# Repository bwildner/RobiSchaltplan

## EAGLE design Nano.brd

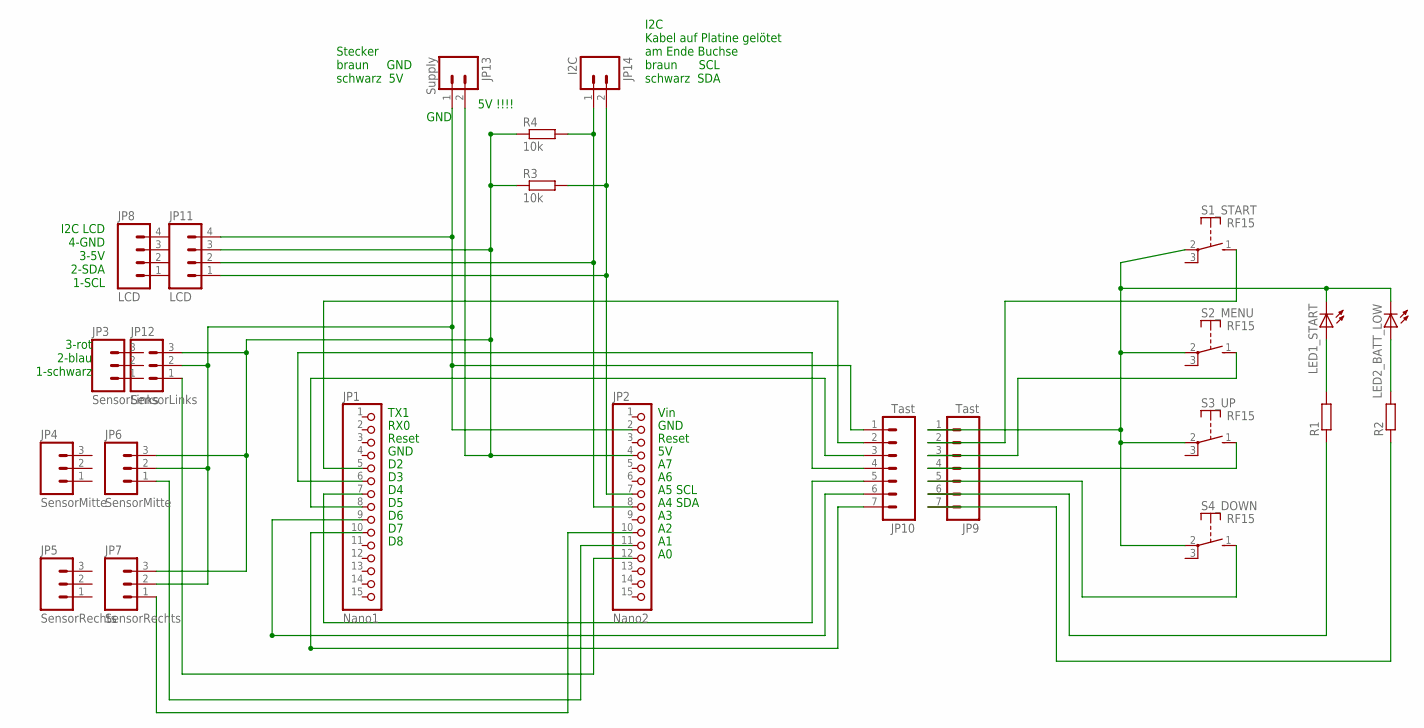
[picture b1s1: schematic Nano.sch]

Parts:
JP1: Nano1; 1X15
JP2: Nano2; 1X15
JP3, JP12: SensorLinks; 1X03_LOCK
JP4, JP6: SensorMitte; 1X03_LOCK
JP5, JP7: SensorRechts; 1X03_LOCK
JP8, JP11: LCD; 1X04_LOCK
JP9, JP10: Tast; 1X07
JP13: Supply; 1X02_LOCK
JP14: I2C; 1X02_LOCK
LED1_START, LED2_BATT_LOW: LED_ELD260; LED_LD260
R1, R2: R-EU_0204/5; 0204/5
R3, R4: 10k; 0204/5
S1_START, S2_MENU, S3_UP, S4_DOWN: RF15

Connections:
GND: JP9.1, LED1_START.K (C), LED2_BATT_LOW.K (C), S1_START.2, S2_MENU.2, S3_UP.2, S4_DOWN.2
unnamed: JP1.5, JP10.2
unnamed: JP1.8, JP10.3
unnamed: JP1.6, JP10.4
unnamed: JP1.7, JP10.5
unnamed: JP9.7, R2.1
unnamed: LED2_BATT_LOW.A, R2.2
unnamed: LED1_START.A, R1.2
unnamed: JP1.9, JP10.6
unnamed: JP2.12, JP12.1
unnamed: JP2.11, JP6.1
unnamed: JP2.10, JP7.1
unnamed: JP2.4, JP6.3, JP7.3, JP11.3, JP12.3, JP13.2, R3.1, R4.1
unnamed: JP2.2, JP6.2, JP7.2, JP10.1, JP11.4, JP12.2, JP13.1
unnamed: JP2.7, JP11.1, JP14.2, R3.2
unnamed: JP2.8, JP11.2, JP14.1, R4.2
unnamed: JP9.2, S1_START.1 (S)
unnamed: JP9.4, S3_UP.1 (S)
unnamed: JP9.3, S2_MENU.1 (S)
unnamed: JP9.5, S4_DOWN.1 (S)
unnamed: JP9.6, R1.1
unnamed: JP1.10, JP10.7

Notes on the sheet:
TX1
RX0
Reset
GND
Vin
A5 SCL
A4 SDA
Stecker braun GND schwarz 5V
5V !!!!
I2C Kabel auf Platine gelötet am Ende Buchse braun SCL schwarz SDA
I2C LCD 4-GND 3-5V 2-SDA 1-SCL
3-rot 2-blau 1-schwarz

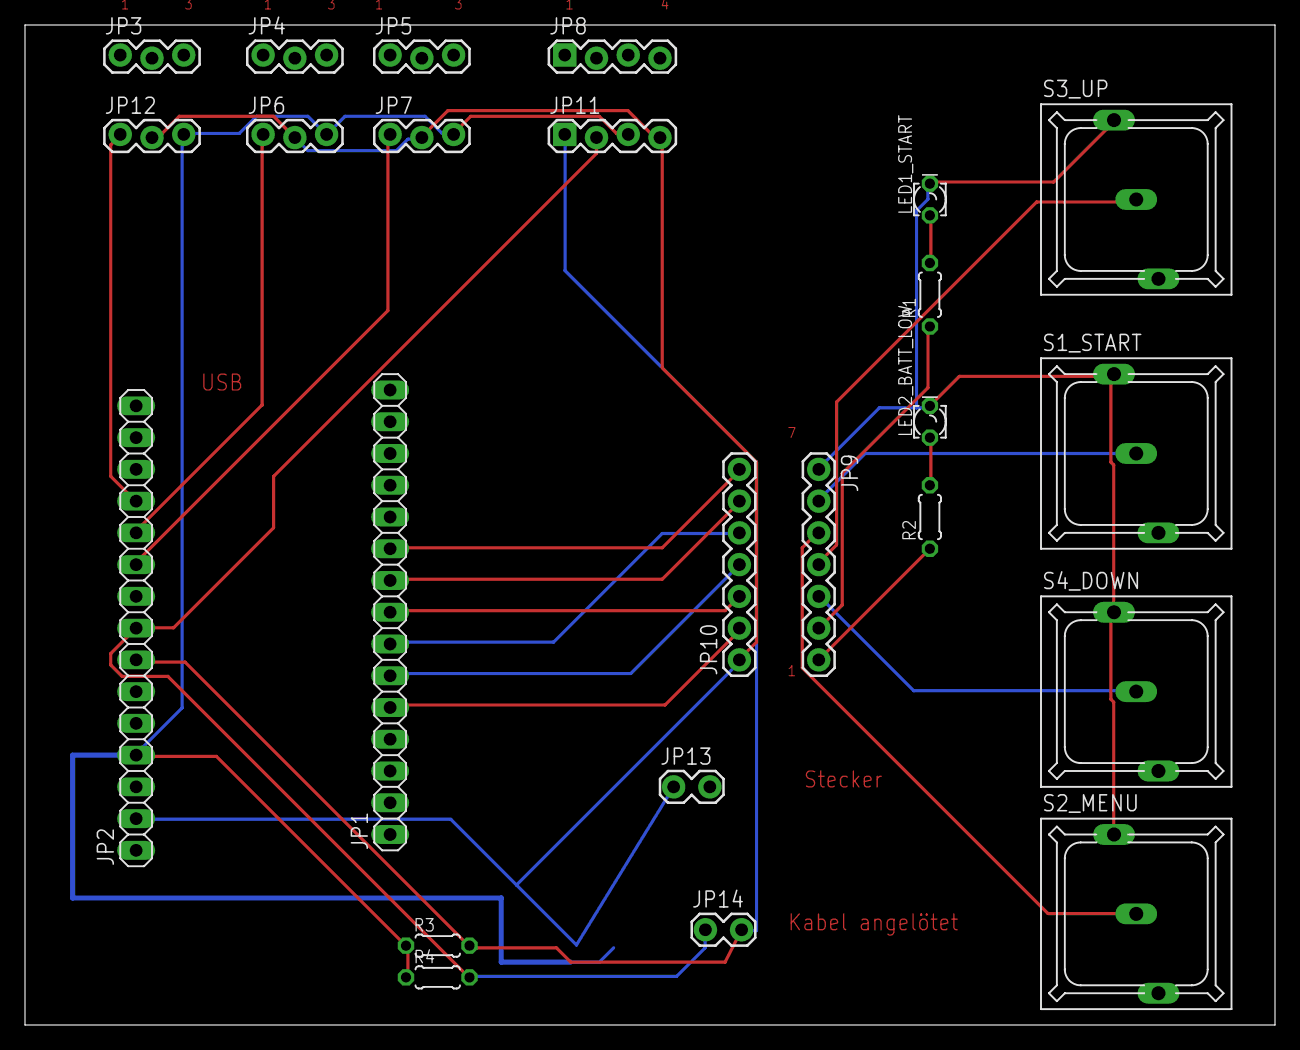
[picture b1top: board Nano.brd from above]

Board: 2 copper layers, 100.0 x 80.0 mm, 24 parts (0 on the bottom side), 22 nets.

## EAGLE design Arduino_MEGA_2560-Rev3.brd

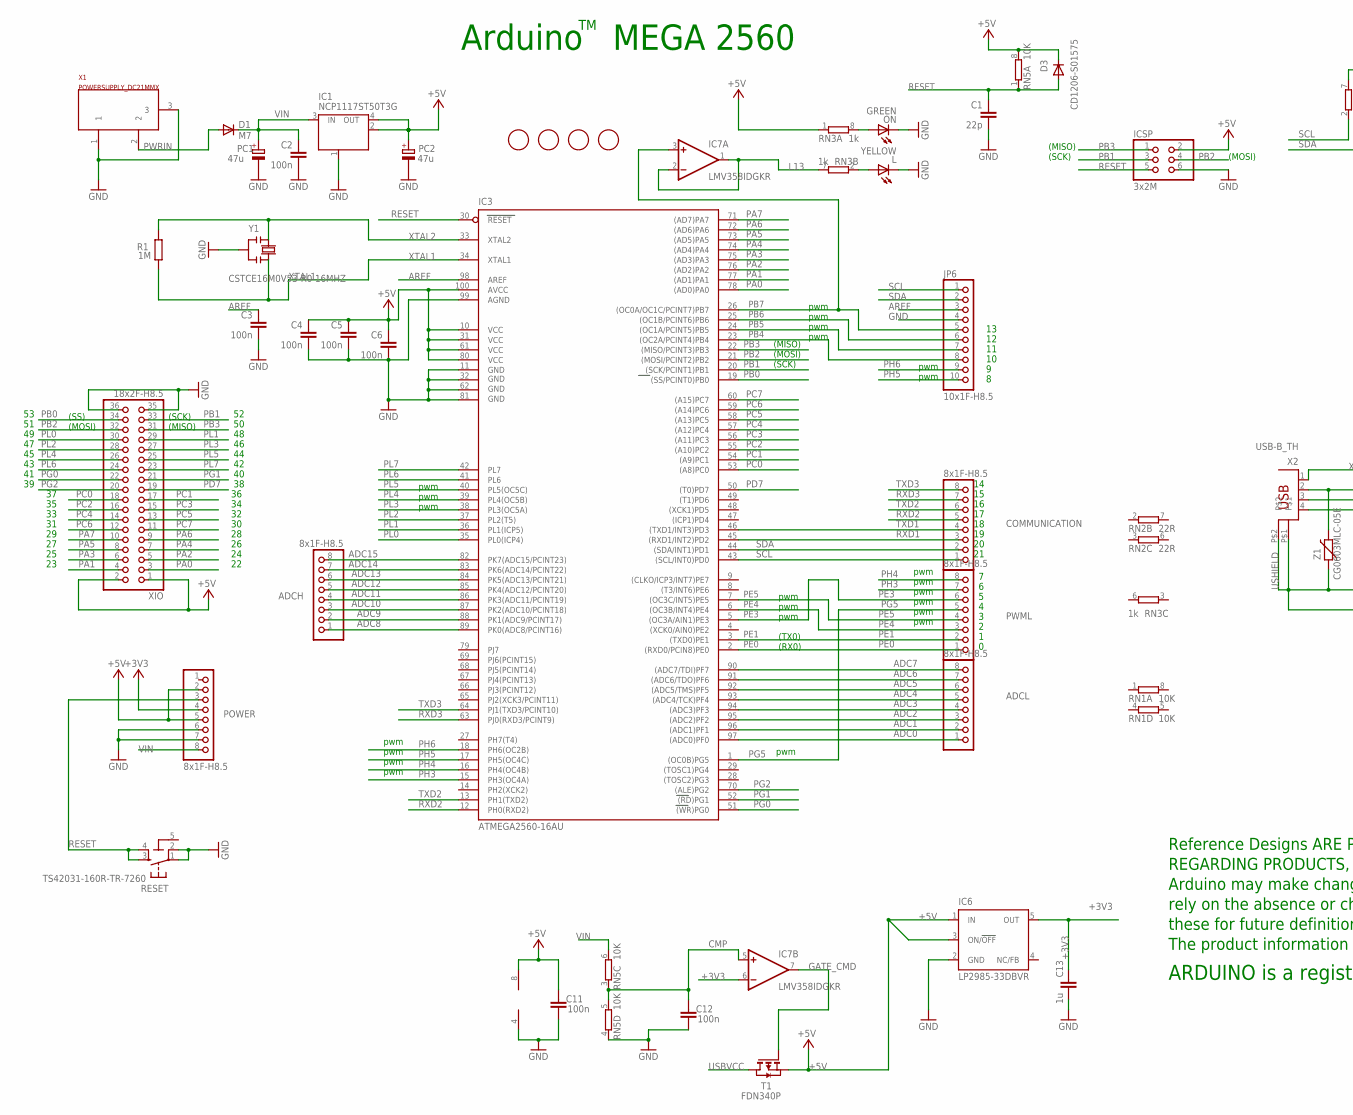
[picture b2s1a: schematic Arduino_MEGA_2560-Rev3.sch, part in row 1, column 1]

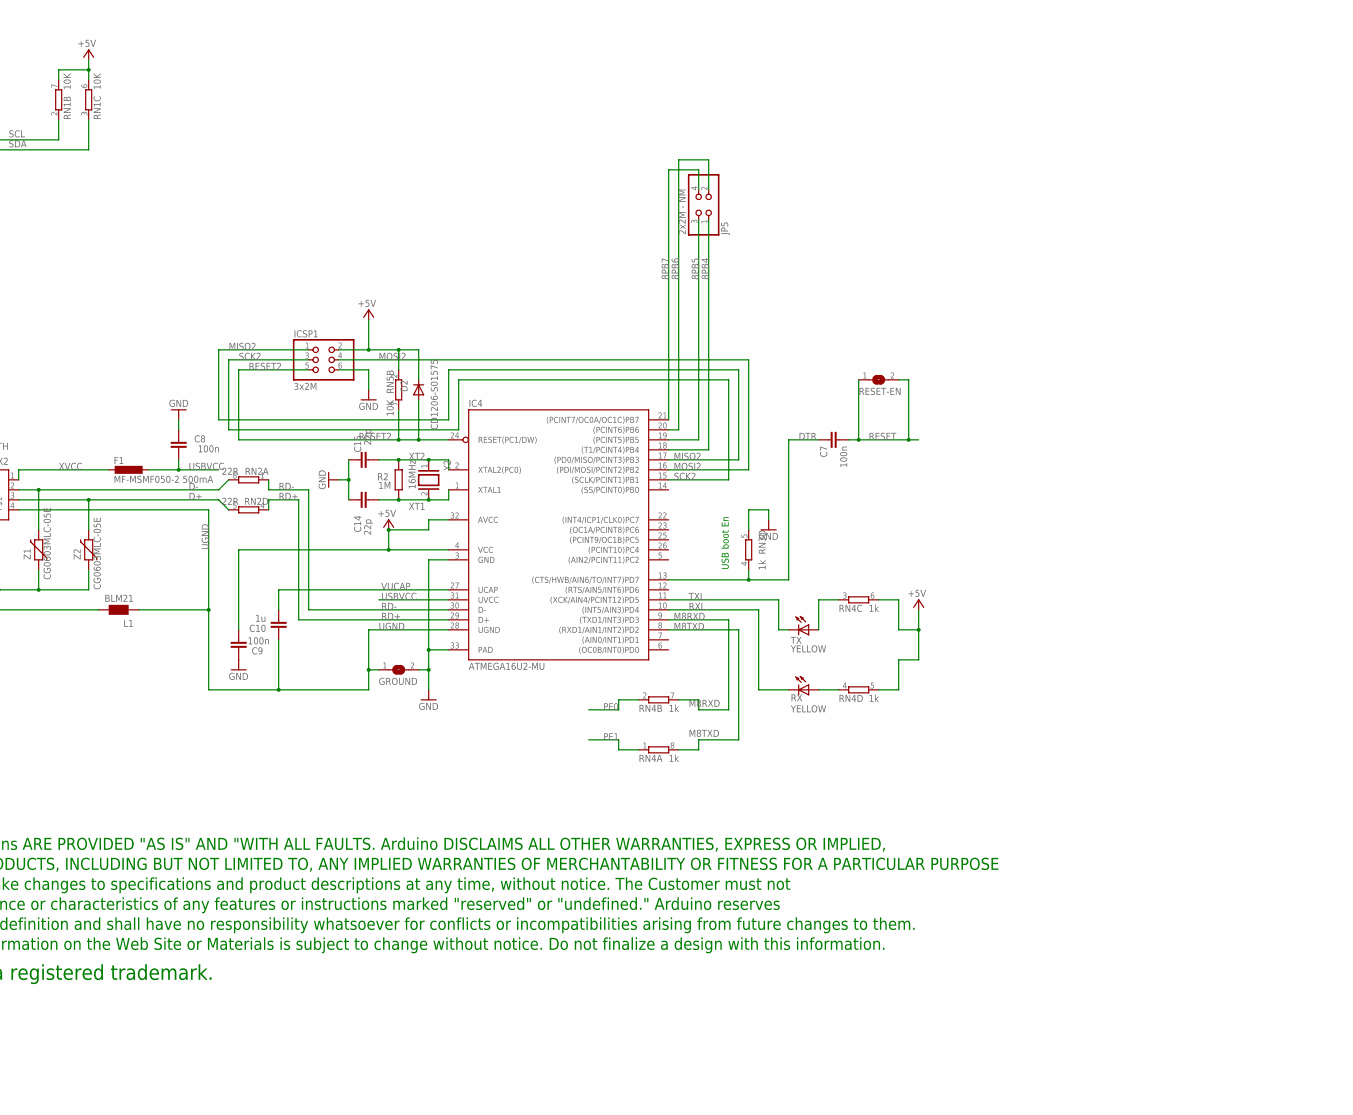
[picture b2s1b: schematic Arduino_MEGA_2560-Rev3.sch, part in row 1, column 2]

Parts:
ADCH: 8x1F-H8.5; 1X08
ADCL: 8x1F-H8.5; 1X08
C1, C14, C15: 22p; C0603-ROUND
C2, C3, C4, C5, C6, C7, C8, C9, C11, C12: 100n; C0603-ROUND
C10, C13: 1u; C0603-ROUND
COMMUNICATION: 8x1F-H8.5; 1X08
D1: M7; SMB
D2, D3: CD1206-S01575; MINIMELF
F1: MF-MSMF050-2 500mA; L1812
FD1, FD2, FD3, FD4: FIDUCIALMOUNT; FIDUCIA-MOUNT
GROUND: SJ
IC1: NCP1117ST50T3G; SOT223
IC3: ATMEGA2560-16AU; TQFP100
IC4: ATMEGA16U2-MU; MLF32
IC6: LP2985-33DBVR; SOT23-DBV
IC7: LMV358IDGKR; MSOP08
ICSP, ICSP1: 3x2M; 2X03
JP5: 2x2M - NM; 2X02
JP6: 10x1F-H8.5; 1X10
L: YELLOW; CHIP-LED0805
L1: BLM21; 0805
ON: GREEN; CHIP-LED0805
PC1, PC2: 47u; PANASONIC_D
POWER: 8x1F-H8.5; 1X08
PWML: 8x1F-H8.5; 1X08
R1, R2: 1M; R0603-ROUND
RESET: TS42031-160R-TR-7260; TS42
RESET-EN: SJ
RN1, RN5: 10K; CAT16
RN2: 22R; CAY16
RN3, RN4: 1k; CAY16
RX: YELLOW; CHIP-LED0805
T1: FDN340P; SOT-23
TX: YELLOW; CHIP-LED0805
U$1: DISCLAIMER
X1: POWERSUPPLY_DC21MMX; POWERSUPPLY_DC-21MM
X2: USB-B_TH; PN61729
XIO: 18x2F-H8.5; 2X18
Y1: CSTCE16M0V53-R0 16MHZ; RESONATOR
Y2: 16MHz; QS
Z1, Z2: CG0603MLC-05E; CT/CN0603

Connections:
5-GND: RESET.5 (5-GND)
8PB4: IC4.18 ((T1/PCINT4)PB4), JP5.1
8PB5: IC4.19 ((PCINT5)PB5), JP5.3
8PB6: IC4.20 ((PCINT6)PB6), JP5.2
8PB7: IC4.21 ((PCINT7/OC0A/OC1C)PB7), JP5.4
+3V3: C13.2, IC6.5 (OUT), IC7.6 (-IN), POWER.4
+5V: C4.1, C5.1, C6.1, C9.1, C11.2, D2.C, D3.C, IC1.2 (OUT), IC1.4 (OUT), IC3.10 (VCC), IC3.31 (VCC1), IC3.61 (VCC2), IC3.80 (VCC3), IC3.100 (AVCC), IC4.4 (VCC), IC4.32 (AVCC), IC6.1 (IN), IC6.3 (ON/!OFF), IC7.8 (V+), ICSP.2, ICSP1.2, PC2.+, POWER.2, POWER.5, RN1.6 (2), RN1.7 (2), RN3.1, RN4.5 (2), RN4.6 (2), RN5.2 (1), RN5.8 (2), T1.2 (S), XIO.1, XIO.2
ADC0: ADCL.1, IC3.97 ((ADC0)PF0)
ADC1: ADCL.2, IC3.96 ((ADC1)PF1)
ADC2: ADCL.3, IC3.95 ((ADC2)PF2)
ADC3: ADCL.4, IC3.94 ((ADC3)PF3)
ADC4: ADCL.5, IC3.93 ((ADC4/TCK)PF4)
ADC5: ADCL.6, IC3.92 ((ADC5/TMS)PF5)
ADC6: ADCL.7, IC3.91 ((ADC6/TDO)PF6)
ADC7: ADCL.8, IC3.90 ((ADC7/TDI)PF7)
ADC8: ADCH.1, IC3.89 (PK0(ADC8/PCINT16))
ADC9: ADCH.2, IC3.88 (PK1(ADC9/PCINT17))
ADC10: ADCH.3, IC3.87 (PK2(ADC10/PCINT18))
ADC11: ADCH.4, IC3.86 (PK3(ADC11/PCINT19))
ADC12: ADCH.5, IC3.85 (PK4(ADC12/PCINT20))
ADC13: ADCH.6, IC3.84 (PK5(ADC13/PCINT21))
ADC14: ADCH.7, IC3.83 (PK6(ADC14/PCINT22))
ADC15: ADCH.8, IC3.82 (PK7(ADC15/PCINT23))
AREF: C3.1, IC3.98 (AREF), JP6.3
CMP: C12.2, IC7.5 (+IN), RN5.3 (1), RN5.5 (2)
D+: RN2.5 (2), X2.3, Z2.2
D-: RN2.8 (2), X2.2, Z1.2
DTR: C7.1, IC4.13 ((CTS/HWB/AIN6/TO/INT7)PD7), RN3.4 (1)
GATE_CMD: IC7.7 (OUT), T1.3 (G)
GND: C1.2, C2.2, C3.2, C4.2, C5.2, C6.2, C8.2, C9.2, C11.1, C12.1, C13.1, C14.2, C15.2, GROUND.2, IC1.1 (GND/ADJ), IC3.11 (GND), IC3.32 (GND1), IC3.62 (GND2), IC3.81 (GND3), IC3.99 (AGND), IC4.3 (GND), IC4.33 (PAD), IC6.2 (GND), IC7.4 (V-), ICSP.6, ICSP1.6, JP6.4, L.C, ON.C, PC1.-, PC2.-, POWER.6, POWER.7, RESET.1, RESET.2, RN3.5 (2), RN5.4 (1), X1.1, X1.3, XIO.35, XIO.36, Y1.2
L13: IC7.1 (OUT), IC7.2 (-IN), RN3.7 (2)
M8RXD: IC4.9 ((TXD1/INT3)PD3), RN4.7 (2)
M8TXD: IC4.8 ((RXD1/AIN1/INT2)PD2), RN4.8 (2)
MISO2: IC4.17 ((PD0/MISO/PCINT3)PB3), ICSP1.1
MOSI2: IC4.16 ((PDI/MOSI/PCINT2)PB2), ICSP1.4
unnamed: L.A, RN3.2 (1)
unnamed: ON.A, RN3.8 (2)
unnamed: RN4.4 (1), RX.A
unnamed: RN4.3 (1), TX.A
PA0: IC3.78 ((AD0)PA0), XIO.3
PA1: IC3.77 ((AD1)PA1), XIO.4
PA2: IC3.76 ((AD2)PA2), XIO.5
PA3: IC3.75 ((AD3)PA3), XIO.6
PA4: IC3.74 ((AD4)PA4), XIO.7
PA5: IC3.73 ((AD5)PA5), XIO.8
PA6: IC3.72 ((AD6)PA6), XIO.9
PA7: IC3.71 ((AD7)PA7), XIO.10
PB0: IC3.19 ((SS/PCINT0)PB0), XIO.34
PB1: IC3.20 ((SCK/PCINT1)PB1), ICSP.3, XIO.33
PB2: IC3.21 ((MOSI/PCINT2)PB2), ICSP.4, XIO.32
PB3: IC3.22 ((MISO/PCINT3)PB3), ICSP.1, XIO.31
PB4: IC3.23 ((OC2A/PCINT4)PB4), JP6.8
PB5: IC3.24 ((OC1A/PCINT5)PB5), JP6.7
PB6: IC3.25 ((OC1B/PCINT6)PB6), JP6.6
PB7: IC3.26 ((OC0A/OC1C/PCINT7)PB7), IC7.3 (+IN), JP6.5
PC0: IC3.53 ((A8)PC0), XIO.18
PC1: IC3.54 ((A9)PC1), XIO.17
PC2: IC3.55 ((A10)PC2), XIO.16
PC3: IC3.56 ((A11)PC3), XIO.15
PC4: IC3.57 ((A12)PC4), XIO.14
PC5: IC3.58 ((A13)PC5), XIO.13
PC6: IC3.59 ((A14)PC6), XIO.12
PC7: IC3.60 ((A15)PC7), XIO.11
PD7: IC3.50 ((T0)PD7), XIO.19
PE0: IC3.2 ((RXD0/PCIN8)PE0), PWML.1, RN4.2 (1)
PE1: IC3.3 ((TXD0)PE1), PWML.2, RN4.1
PE3: IC3.5 ((OC3A/AIN1)PE3), PWML.6
PE4: IC3.6 ((OC3B/INT4)PE4), PWML.3
PE5: IC3.7 ((OC3C/INT5)PE5), PWML.4
PG0: IC3.51 ((WR)PG0), XIO.22
PG1: IC3.52 ((RD)PG1), XIO.21
PG2: IC3.70 ((ALE)PG2), XIO.20
PG5: IC3.1 ((OC0B)PG5), PWML.5
PH3: IC3.15 (PH3(OC4A)), PWML.7
PH4: IC3.16 (PH4(OC4B)), PWML.8
PH5: IC3.17 (PH5(OC4C)), JP6.10
PH6: IC3.18 (PH6(OC2B)), JP6.9
PL0: IC3.35 (PL0(ICP4)), XIO.30
PL1: IC3.36 (PL1(ICP5)), XIO.29
PL2: IC3.37 (PL2(T5)), XIO.28
PL3: IC3.38 (PL3(OC5A)), XIO.27
PL4: IC3.39 (PL4(OC5B)), XIO.26
PL5: IC3.40 (PL5(OC5C)), XIO.25
PL6: IC3.41 (PL6), XIO.24
PL7: IC3.42 (PL7), XIO.23
PWRIN: D1.A, X1.2
RD+: IC4.29 (D+), RN2.4 (1)
RD-: IC4.30 (D-), RN2.1
RESET: C1.1, C7.2, D3.A, IC3.30 (RESET), ICSP.5, POWER.3, RESET.3, RESET.4, RESET-EN.1, RESET-EN.2, RN5.1
RESET2: D2.A, IC4.24 (RESET(PC1/DW)), ICSP1.5, RN5.7 (2)
RXD1: COMMUNICATION.3, IC3.45 ((RXD1/INT2)PD2)
RXD2: COMMUNICATION.5, IC3.12 (PH0(RXD2))
RXD3: COMMUNICATION.7, IC3.63 (PJ0(RXD3/PCINT9))
RXL: IC4.10 ((INT5/AIN3)PD4), RX.C
SCK2: IC4.15 ((SCLK/PCINT1)PB1), ICSP1.3
SCL: COMMUNICATION.1, IC3.43 ((SCL/INT0)PD0), JP6.1, RN1.2 (1)
SDA: COMMUNICATION.2, IC3.44 ((SDA/INT1)PD1), JP6.2, RN1.3 (1)
TXD1: COMMUNICATION.4, IC3.46 ((TXD1/INT3)PD3)
TXD2: COMMUNICATION.6, IC3.13 (PH1(TXD2))
TXD3: COMMUNICATION.8, IC3.64 (PJ1(TXD3/PCINT10))
TXL: IC4.11 ((XCK/AIN4/PCINT12)PD5), TX.C
UGND: C10.2, GROUND.1, IC4.28 (UGND), L1.1, X2.4
USBVCC: C8.1, F1.1, IC4.31 (UVCC), T1.1 (D)
USHIELD: L1.2, X2.P$1, X2.P$2, Z1.1, Z2.1
VIN: C2.1, D1.C, IC1.3 (IN), PC1.+, POWER.8, RN5.6 (2)
VUCAP: C10.1, IC4.27 (UCAP)
XT1: C14.1, IC4.1 (XTAL1), R2.1, Y2.2
XT2: C15.1, IC4.2 (XTAL2(PC0)), R2.2, Y2.1
XTAL1: IC3.34 (XTAL1), R1.1, Y1.3
XTAL2: IC3.33 (XTAL2), R1.2, Y1.1
XVCC: F1.2, X2.1

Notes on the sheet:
Arduino MEGA 2560
(SCK)
(MISO)
(MOSI)
pwm
(TX0)
(RX0)
(SS)
USB boot En

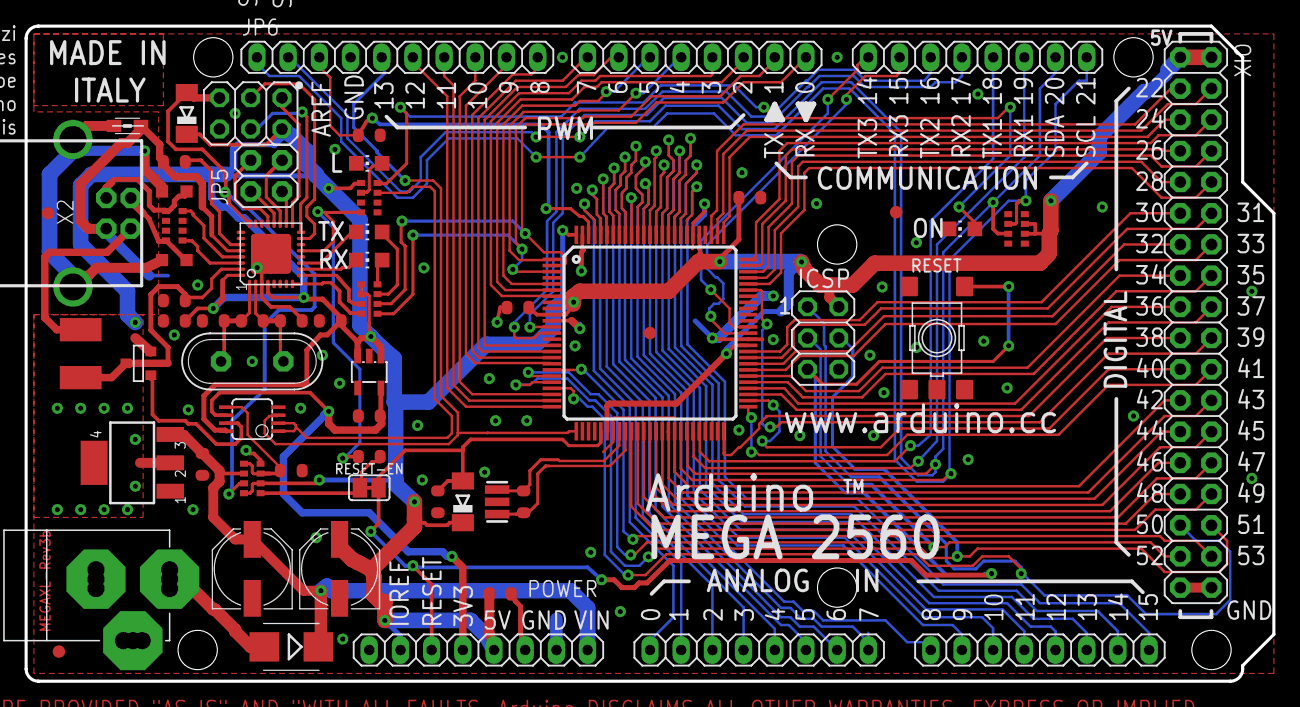
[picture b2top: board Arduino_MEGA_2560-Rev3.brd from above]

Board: 2 copper layers, 101.6 x 53.3 mm, 63 parts (1 on the bottom side), 110 nets.

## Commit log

2017-03-11 Erstes Upload

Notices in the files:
parts and their libraries:
SparkFun-Connectors: Licensing: Creative Commons ShareAlike 4.0 International - https://creativecommons.org/licenses/by-sa/4.0
